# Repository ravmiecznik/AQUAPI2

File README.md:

# AQUAPI2

## Aquarium controller based on RaspberryPi Zero2 and Arduino.<br>
The controller supports:<br>

* PH control with use of <a href=https://botland.store/gravity-temperature-sensors/5874-dfrobot-gravity-ph-analog-sensormeter-5903351243513.html>DFORBOT PROBE</a>
and CO2 injection system equipped with CO2 electric valve
<br>

* Temperature reading with DS12B20 digital thermometer sensor [<a href="https://www.circuitbasics.com/raspberry-pi-ds18b20-temperature-sensor-tutorial/">how to</a>] or any analog thermometer accessible via Arduino board

* Control devices and lighting with 8 channel Relay

## Other components and software

* Arduino MINI PRO

* Arduino ISP programming done with RaspberryPI [<a href="https://learn.adafruit.com/program-an-avr-or-arduino-using-raspberry-pi-gpio-pins">Adafruit manual</a>]

* Plotly library <a href="https://plotly.com/python/">PLOTLY</a>

* Circuit designed in Eagle [Version 0]

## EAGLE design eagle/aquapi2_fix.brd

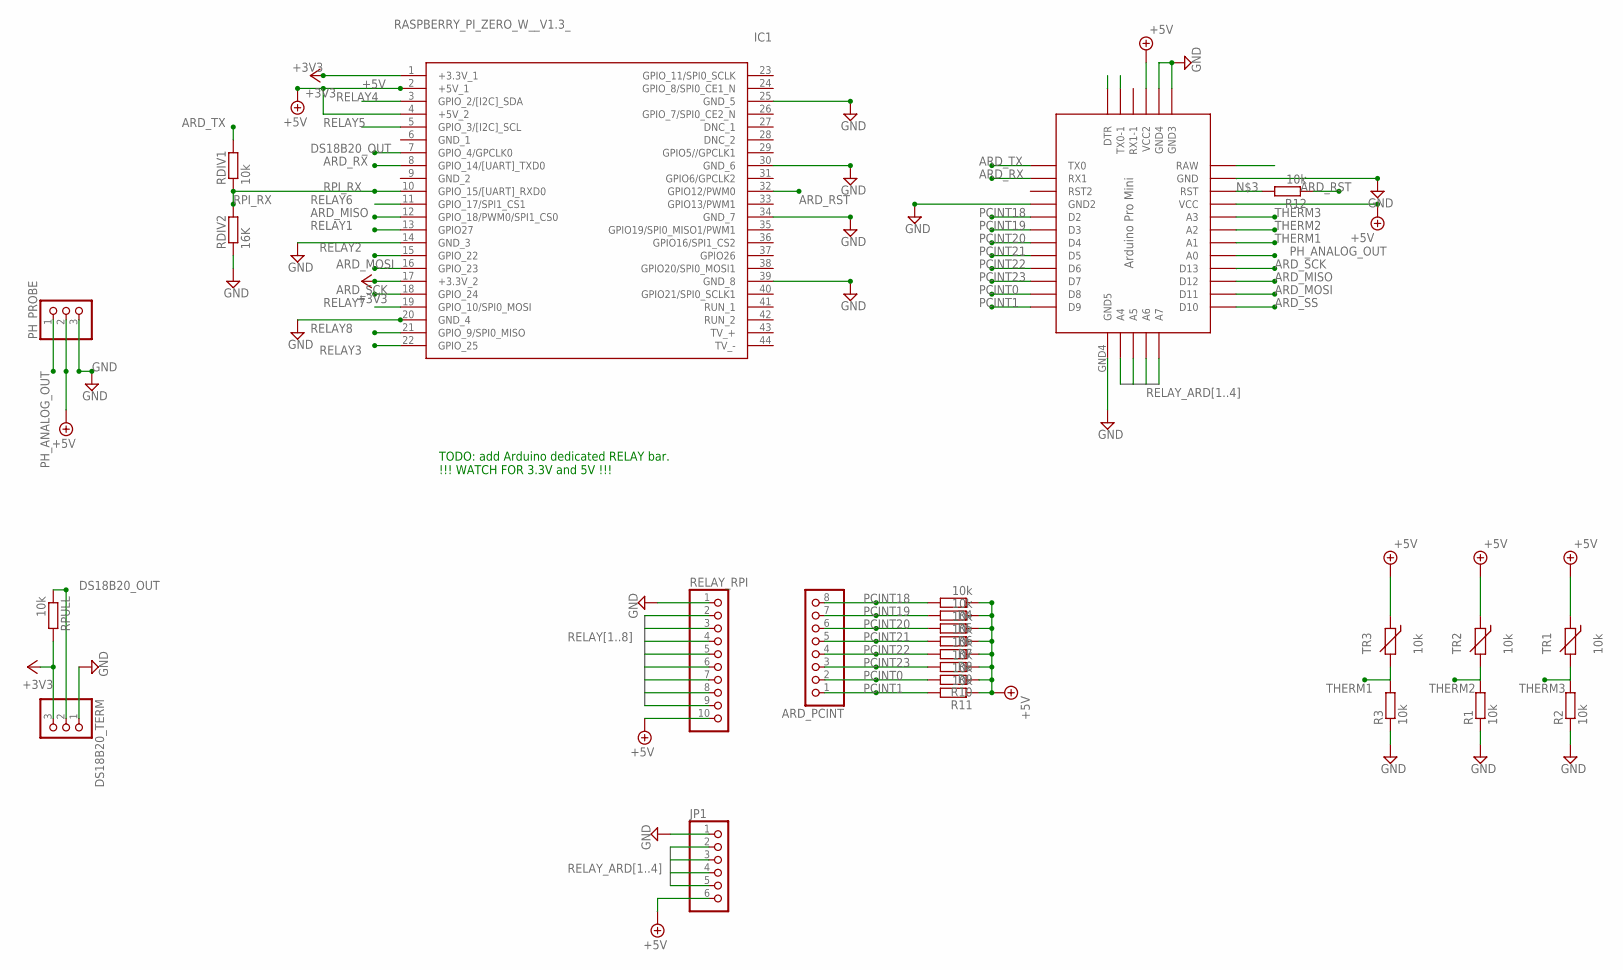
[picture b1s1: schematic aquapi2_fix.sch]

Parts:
ARD_PCINT: PINHD-1X8; 1X08
DS18B20_TERM: PINHD-1X3; 1X03
IC1: RASPBERRY_PI_ZERO_W__V1.3_; RASPBERRYPIZEROWV13
JP1: PINHD-1X6; 1X06
PH_PROBE: PINHD-1X3; 1X03
R1, R2, R3, R4, R5, R6, R7, R8, R9, R10, R11, R12: 10k; R0805
RDIV1: 10k; R0805
RDIV2: 16K; R0805
RELAY_RPI: PINHD-1X10; 1X10
RPULL: 10k; R0805
TR1, TR2, TR3: 10k; RS-2,5
U$2: PRO-MINI

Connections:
+3V3: DS18B20_TERM.3, IC1.1 (+3.3V_1), IC1.17 (+3.3V_2), RPULL.2
+5V: IC1.2 (+5V_1), IC1.4 (+5V_2), JP1.6, PH_PROBE.2, R4.1, R5.1, R6.1, R7.1, R8.1, R9.1, R10.1, R11.1, RELAY_RPI.10, TR1.1, TR2.1, TR3.1, U$2.VCC, U$2.VCC1 (VCC2)
ARD_MISO: IC1.12 (GPIO_18/PWM0/SPI1_CS0), U$2.D12
ARD_MOSI: IC1.16 (GPIO_23), U$2.D11
ARD_RST: IC1.32 (GPIO12/PWM0), R12.1
ARD_RX: IC1.8 (GPIO_14/[UART]_TXD0), U$2.RX1
ARD_SCK: IC1.18 (GPIO_24), U$2.D13
ARD_SS: U$2.D10
ARD_TX: RDIV1.2, U$2.TX0
DS18B20_OUT: DS18B20_TERM.2, IC1.7 (GPIO_4/GPCLK0), RPULL.1
GND: DS18B20_TERM.1, IC1.14 (GND_3), IC1.20 (GND_4), IC1.25 (GND_5), IC1.30 (GND_6), IC1.34 (GND_7), IC1.39 (GND_8), JP1.1, PH_PROBE.3, R1.1, R2.1, R3.1, RDIV2.1, RELAY_RPI.1, U$2.GND1 (GND2), U$2.GND2 (GND4), U$2.GND3, U$2.GND4 (GND5)
unnamed: R12.2, U$2.RST
PCINT0: ARD_PCINT.2, R10.2, U$2.D8
PCINT1: ARD_PCINT.1, R11.2, U$2.D9
PCINT18: ARD_PCINT.8, R4.2, U$2.D2
PCINT19: ARD_PCINT.7, R5.2, U$2.D3
PCINT20: ARD_PCINT.6, R6.2, U$2.D4
PCINT21: ARD_PCINT.5, R7.2, U$2.D5
PCINT22: ARD_PCINT.4, R8.2, U$2.D6
PCINT23: ARD_PCINT.3, R9.2, U$2.D7
PH_ANALOG_OUT: PH_PROBE.1, U$2.A0
RELAY1: IC1.13 (GPIO27), RELAY_RPI.2
RELAY2: IC1.15 (GPIO_22), RELAY_RPI.3
RELAY3: IC1.22 (GPIO_25), RELAY_RPI.4
RELAY4: IC1.3 (GPIO_2/[I2C]_SDA), RELAY_RPI.5
RELAY5: IC1.5 (GPIO_3/[I2C]_SCL), RELAY_RPI.6
RELAY6: IC1.11 (GPIO_17/SPI1_CS1), RELAY_RPI.7
RELAY7: IC1.19 (GPIO_10/SPI0_MOSI), RELAY_RPI.8
RELAY8: IC1.21 (GPIO_9/SPI0_MISO), RELAY_RPI.9
RELAY_ARD1: JP1.2, U$2.A4
RELAY_ARD2: JP1.3, U$2.A5
RELAY_ARD3: JP1.4, U$2.A6
RELAY_ARD4: JP1.5, U$2.A7
RPI_RX: IC1.10 (GPIO_15/[UART]_RXD0), RDIV1.1, RDIV2.2
THERM1: R3.2, TR3.2, U$2.A1
THERM2: R1.2, TR2.2, U$2.A2
THERM3: R2.2, TR1.2, U$2.A3

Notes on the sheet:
TODO: add Arduino dedicated RELAY bar. !!! WATCH FOR 3.3V and 5V !!!

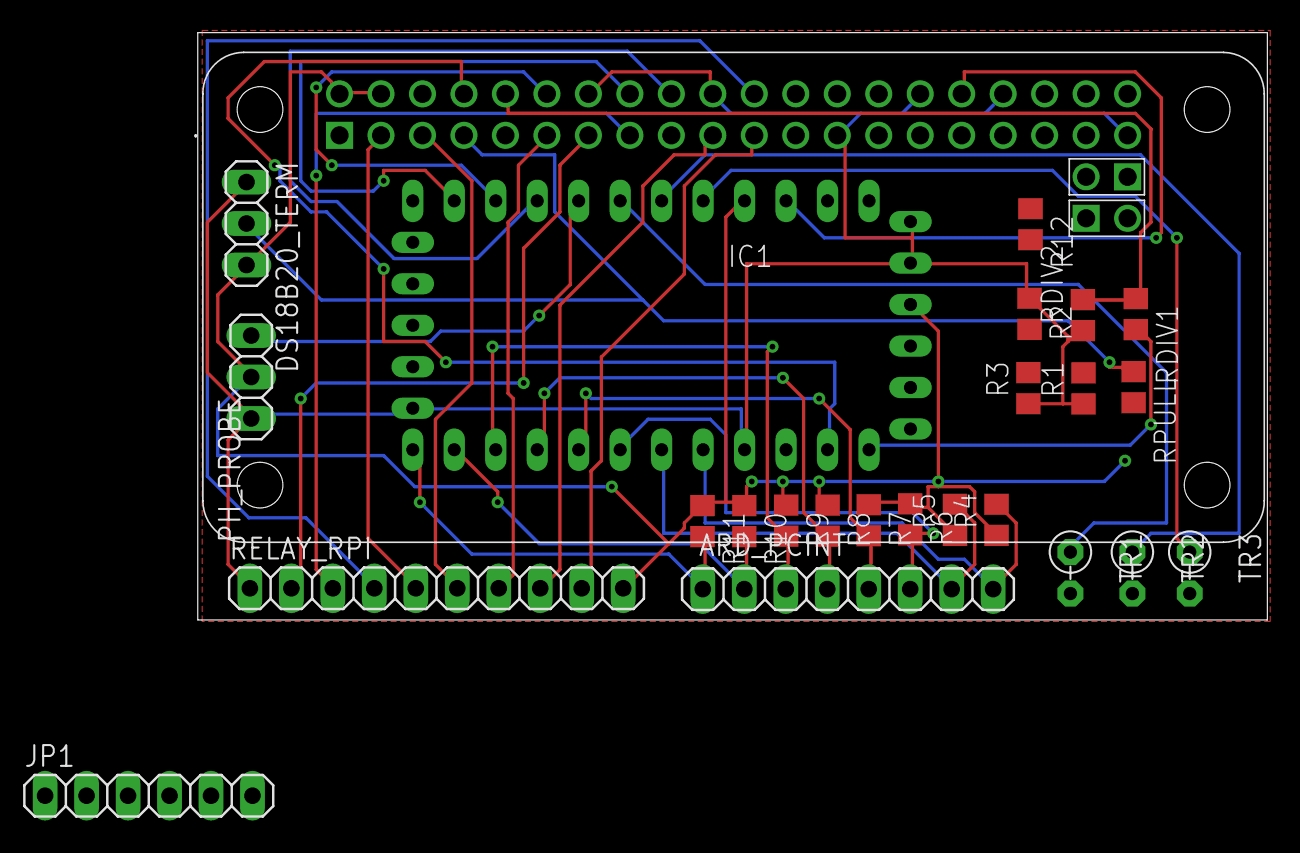
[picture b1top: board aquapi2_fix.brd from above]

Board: 2 copper layers, 65.5 x 36.0 mm, 25 parts (1 on the bottom side), 36 nets.

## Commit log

2022-11-06 init commit
2022-11-06 needed eagle libs added
2022-11-06 relayx8 lib added
2022-11-06 readme
2022-11-06 schemtic added
2022-11-06 bigger schematic
2022-11-06 relay pic
2022-11-06 plotly img added
2022-11-06 readme update
2022-11-06 arudino device lib fixed
2023-03-28 Squashed commit of the following:
    commit 7dce77e1b018337bae77b73dfeb2fe2afd6dd7fb
    Author: rafal <ravmiecznk@gmail.com>
    Date: Mon Mar 27 18:15:28 2023 +0200
    new constructor from struct
    commit 8f6d84a0210c76b2bc0acb519426c939a0a5c33f
    Author: rafal <ravmiecznk@gmail.com>
2023-03-28 use c++ standard
2023-04-07 Squashed commit of the following:
    cmd line POC
    commit 337e95aa13cad48c1064047ce5c9ad90a4095ac0
    Author: rafal <ravmiecznk@gmail.com>
    Date: Fri Apr 7 17:02:08 2023 +0200
    poc works
    commit 96e2bba8cf86e2d1e8c289a96239566a88c918fa
2023-04-07 Squashed commit of the following:
    commit 07ba2ba10c22c423c97b60808b4a4e2224b826f9
    Author: rafal <ravmiecznk@gmail.com>
    Date: Fri Apr 7 22:12:36 2023 +0200
    tested version of cbuffer lib
2023-04-07 get input added
2023-04-08 generic register definition added
2023-04-08 ISRFunctor added, null_function def added
2023-04-08 AdcHandler template added
2023-04-08 formatting fix
2023-04-08 docstring update
2023-04-08 Timer1 can be started
2023-04-08 OCR1A template works
2023-04-14 reserved fields are unnamed
2023-06-17 init version of timers, terminal support POC
2023-06-17 generic_register refactor to register_descriptor
2023-06-17 code cleanup,
2023-06-17 bug fix: adc rosult stored sum instead of mean
2023-06-17 code cleanup
2023-06-18 fix for ADC interrupt enable, fix for 'leaking' ADC results to adjacent ports
2023-06-18 short ADC description added
2023-06-18 ignores added
2023-06-18 settings dir removed
2023-06-18 new ignore added
2023-06-18 screen manipulations added
2023-06-18 comment removed
2023-07-02 new ingnores added
2023-07-02 screen support initial version
2023-07-02 abstract timer added
2023-07-02 ignore .cproject
2023-07-02 timer can be started, can count hours, minutes, seconds, ms in Time object
2023-07-03 timer can count time, TOI interrupt reworked
2023-07-03 todos added
2023-07-07 Squashed commit of the following:
    commit 798ce41465e0510e75b4520c080c88b3ab18497c
    Author: rafal <ravmiecznk@gmail.com>
    Date: Fri Jul 7 14:03:10 2023 +0200
    use microseconds to improve timer accuracy, elimates increasing timer error over time
    commit b00f4a703aaf7847080440523ae8438c521330d4
    Author: rafal <ravmiecznk@gmail.com>
